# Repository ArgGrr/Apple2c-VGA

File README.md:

# Apple2cVGA

I have a PAL Apple 2c which does not produce colour on the composite output.
I made this project to learn about FPGAs and generate a nice VGA image from the Apple 2c video expansion port.

Supports:
- 40 & 80 column text in white. This includes the text in mixed graphics + text modes.
- GR & DGR colours
- HGR colours
- DHGR colours, including AppleWin-like sub-pixel rendering.

It is probably just easier to say it supports pixel accurate video output, but where text mode is drawn monochrome by default.

Various rendering modes, including:

0.  Monochrome (white)
1.  Monochrome (green)
2.  CREF mode
3.  140x192 resolution
4.  580x192 16 Colours no white text
5.  580x192 16 Colours, white text in tex/mixed mode. Default.
6.  Test pattern
7.  Monitor alignment pattern

Brief outline of how it works:
1. Track the A2 blanking signal, detect the horizontal and vertical blanking pulses, use in conjunction with 14MHZ clock to figure out horizontal pixel and vertical line counters.
2. Store the SERDATA bits in groups of 4, aligned to the CREF cycle, into the block RAM. Additionally, store the value of !GR at the start of each line, to determine if the line is TEXT or graphics mode.
3. Generate in a VGA sync module running from the VGA clock, horizontal pixel and vertical line counters.
4. Draw the data from the block RAM, depending on the rendering mode selected. Renders a 580 x 382 image, whith some padding before and after each line, and doubling the lines, onto a 640x480 VGA screen.

Verilog project done in [IceStudio](https://icestudio.io/).

Parts required:
- TinyFPGA BX
- 5v to 3v3  4 channel logic line level converter
- 12v to 5v regulator
- VGA pixel clock resonator, 25Mhz or there abouts. Better if it runs from 3.3v, otherwise you will need to route it through logic level converter.
- Bunch of resistors for the colour "DAC"
- Push button to change rendering mode

My design draws less than 30mA from the 12v line from the expansion port.

Points of interest:
- The NTSC Colourburst is aligned to the blanking output from the machine. Even though HGR and DHGR lines start at different times due to the different pixel clocks, if you count from the unblanking, you can infer the pixel colour later on. Therefore we don't need to store any CREF information in the block RAM.
- CREF rendering mode demonstrates this. Squint at it and the colours sort of match.
- By drawing DHGR 560x192 correctly, you get GR and HGR rendering for free.
- The sub pixel rendering mode is very close if not 100% the same as the Apple2 Win emulator, but I have no hardware (RGB Monitor etc) to reference it against.
- Because the Apple 2 TEXT or GRAPHICS mode is stored per line, things like Crazy Cycles 2c do not look exactly the same as a real machine. I.e. if it is drawing a small TEXT section at the start of a line, the whole line will be drawn black & white. This is an extreme case and I can live with it.
- The 140x192 rendering mode is bugged, the edges of the frame bleed out to the edges of the screen.
- 80col text is only really readable when rendered white / monochrome because of the sub pixel rendering mode, no doubt the same situations occur with a monitor.

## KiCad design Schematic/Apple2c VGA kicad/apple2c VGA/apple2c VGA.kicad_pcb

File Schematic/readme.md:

LibrePCB Schematic project. Work in progress.

Ports have swapped while I figure out the best layout.

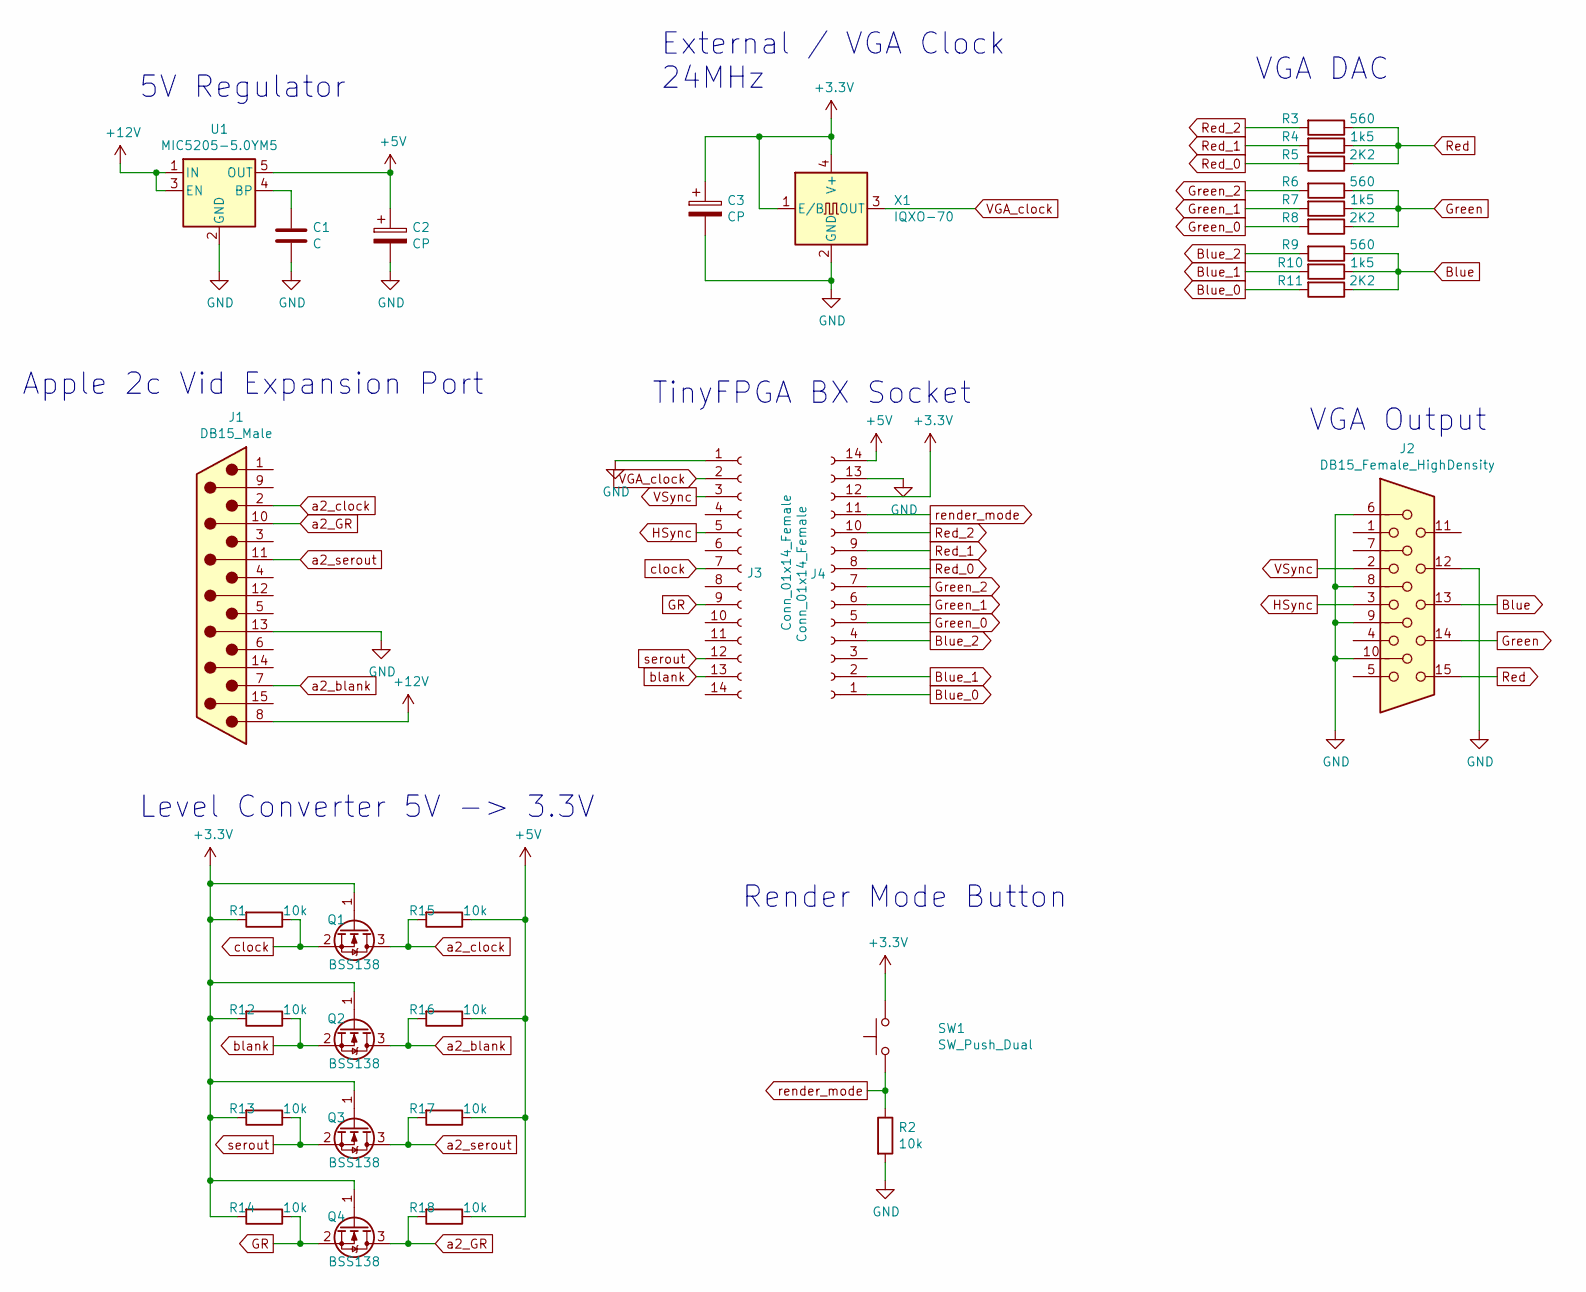
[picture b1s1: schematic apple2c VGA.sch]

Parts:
C1: C; C_0805_2012Metric
C2, C3: CP; C_0805_2012Metric
J1: DB15_Male; DSUB-15_Male_Horizontal_P2.77x2.84mm_EdgePinOffset4.94mm_Ho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
J2: DB15_Female_HighDensity; DSUB-15-HD_Female_Horizontal_P2.29x1.98mm_EdgePinOffset3.03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
J3, J4: Conn_01x14_Female; PinSocket_1x14_P2.54mm_Vertical
Q1, Q2, Q3, Q4: BSS138; SOT-23
R1, R2, R12, R13, R14, R15, R16, R17, R18: 10k; R_0805_2012Metric
R3, R6, R9: 560; R_0805_2012Metric
R4, R7, R10: 1k5; R_0805_2012Metric
R5, R8, R11: 2K2; R_0805_2012Metric
SW1: SW_Push_Dual; SW_PUSH-12mm
U1: MIC5205-5.0YM5; SOT-23-5_HandSoldering
X1: IQXO-70; Oscillator_SMD_IQD_IQXO70-4Pin_7.5x5.0mm

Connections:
+3V3: C3.1, J4.12, Q1.1 (G), Q2.1 (G), Q3.1 (G), Q4.1 (G), R1.2, R12.2, R13.2, R14.2, SW1.2, X1.1 (E/B), X1.4 (V+)
+5V: C2.1, J4.14, R15.1, R16.1, R17.1, R18.1, U1.5 (OUT)
+12V: J1.8, U1.1 (IN), U1.3 (EN)
Blue: J2.13, R9.1, R10.1, R11.1
Blue_0: J4.1, R11.2
Blue_1: J4.2, R10.2
Blue_2: J4.4, R9.2
GND: C1.2, C2.2, C3.2, J1.13, J2.6, J2.8, J2.9, J2.10, J2.12, J3.1, J4.13, R2.2, U1.2 (GND), X1.2 (GND)
GR: J3.9, Q4.2 (S), R14.1
Green: J2.14, R6.1, R7.1, R8.1
Green_0: J4.5, R8.2
Green_1: J4.6, R7.2
Green_2: J4.7, R6.2
HSync: J2.3, J3.5
unnamed: C1.1, U1.4 (BP)
Red: J2.15, R3.1, R4.1, R5.1
Red_0: J4.8, R5.2
Red_1: J4.9, R4.2
Red_2: J4.10, R3.2
VGA_clock: J3.2, X1.3 (OUT)
VSync: J2.2, J3.3
a2_GR: J1.10, Q4.3 (D), R18.2
a2_blank: J1.7, Q2.3 (D), R16.2
a2_clock: J1.2, Q1.3 (D), R15.2
a2_serout: J1.11 (P111), Q3.3 (D), R17.2
blank: J3.13, Q2.2 (S), R12.1
clock: J3.7, Q1.2 (S), R1.1
render_mode: J4.11, R2.1, SW1.1
serout: J3.12, Q3.2 (S), R13.1

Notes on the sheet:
Level Converter 5V -> 3.3V
Render Mode Button
5V Regulator
External / VGA Clock 24MHz
VGA DAC
VGA Output
TinyFPGA BX Socket
Apple 2c Vid Expansion Port

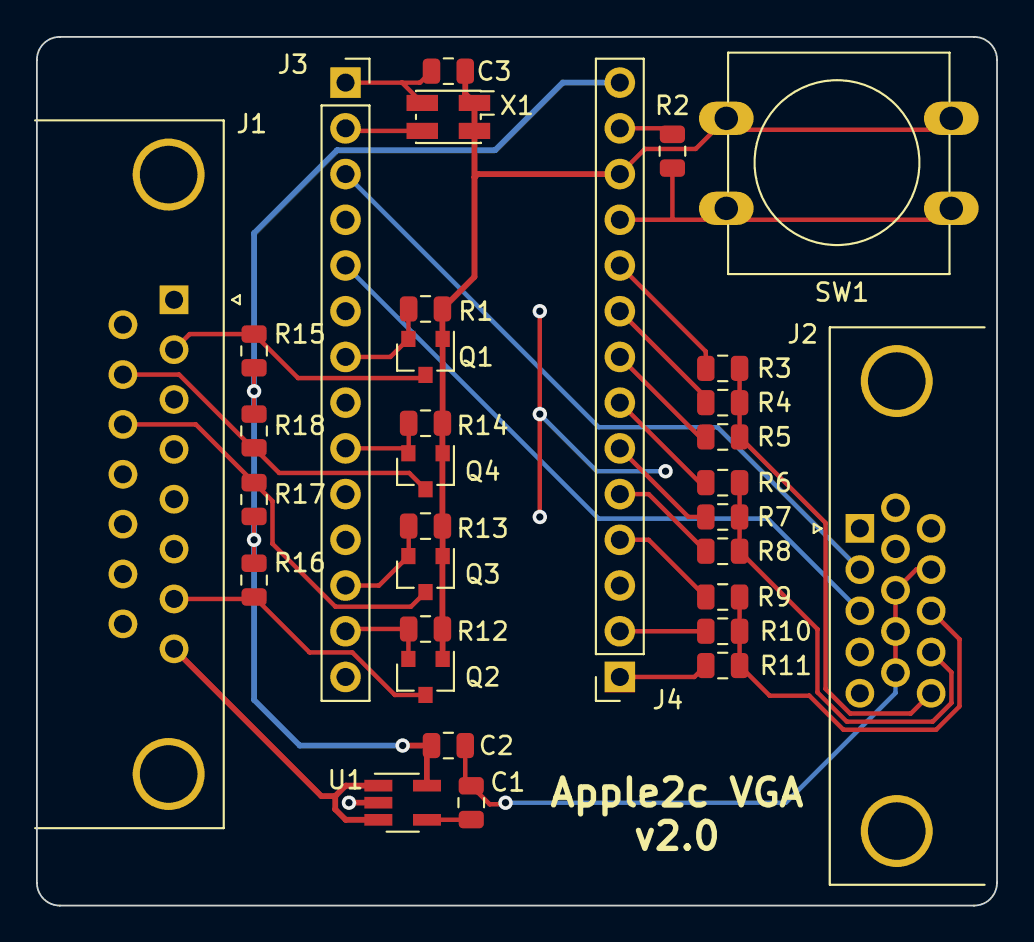
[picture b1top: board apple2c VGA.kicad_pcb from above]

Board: 2 copper layers, 53.3 x 48.3 mm, 32 parts (0 on the bottom side), 29 nets.

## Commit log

2020-02-16 :tada: Added .gitattributes
2020-02-16 v1
    Initial dump of v1 files.
2020-02-16 Add vb project
    Add VB project which collapses all 4096 sub pixel rendering cases down
    to ~159 unique options.
2020-02-16 Create LICENSE
2020-02-16 Add some happy snaps
2020-02-16 Schematic Libraries
2020-02-18 Add 3d models
2020-02-23 Schematic, 3d model updates
    Semi-finalised the schematic. Pending parts on order and attempted build.
    Working on 3d model for DB19 plug for disk drive port, sd card project.
2020-02-24 Case
    Started building a case, pending first build of the board of course.
2020-02-26 Adding standalone reset button cap
2020-02-28 Updated mode button.
2020-03-02 working on case
2020-03-04 Working on case for smartport sd device
2020-03-09 Various updates
2020-06-28 First PCB and build done, reworking.
    Built first version, had some issues. Reworking the PCB design in KiCAD. FPGA tweaked slightly to fix a colour bug and to remap IO.
2020-06-28 Added some video captures.
    I don't have a capture, took these with my phone, cropped and recompressed.
2020-06-28 Tidy up
2020-07-12 test
